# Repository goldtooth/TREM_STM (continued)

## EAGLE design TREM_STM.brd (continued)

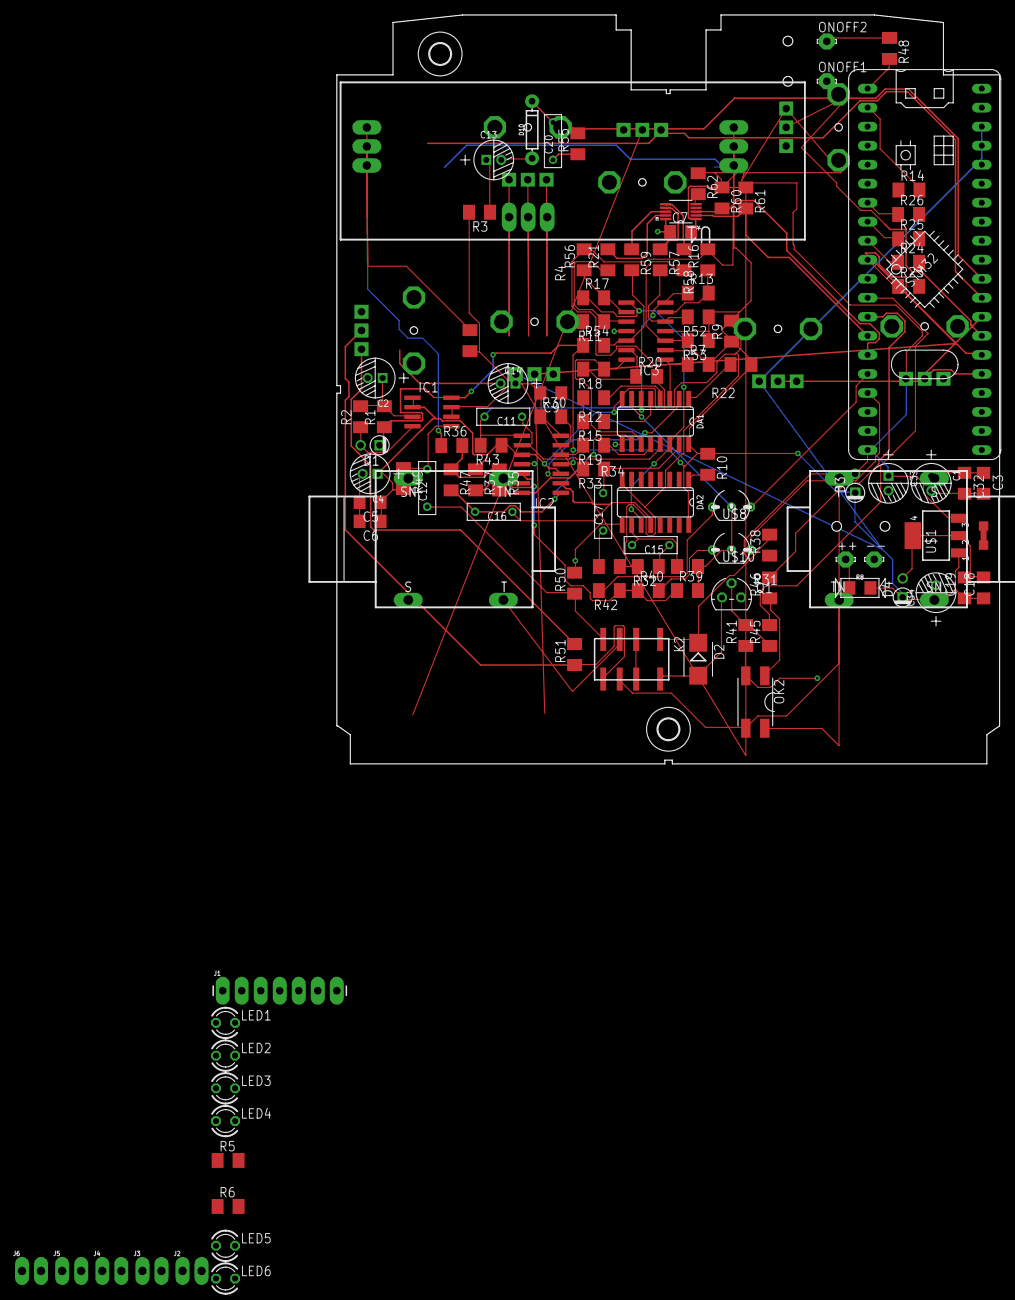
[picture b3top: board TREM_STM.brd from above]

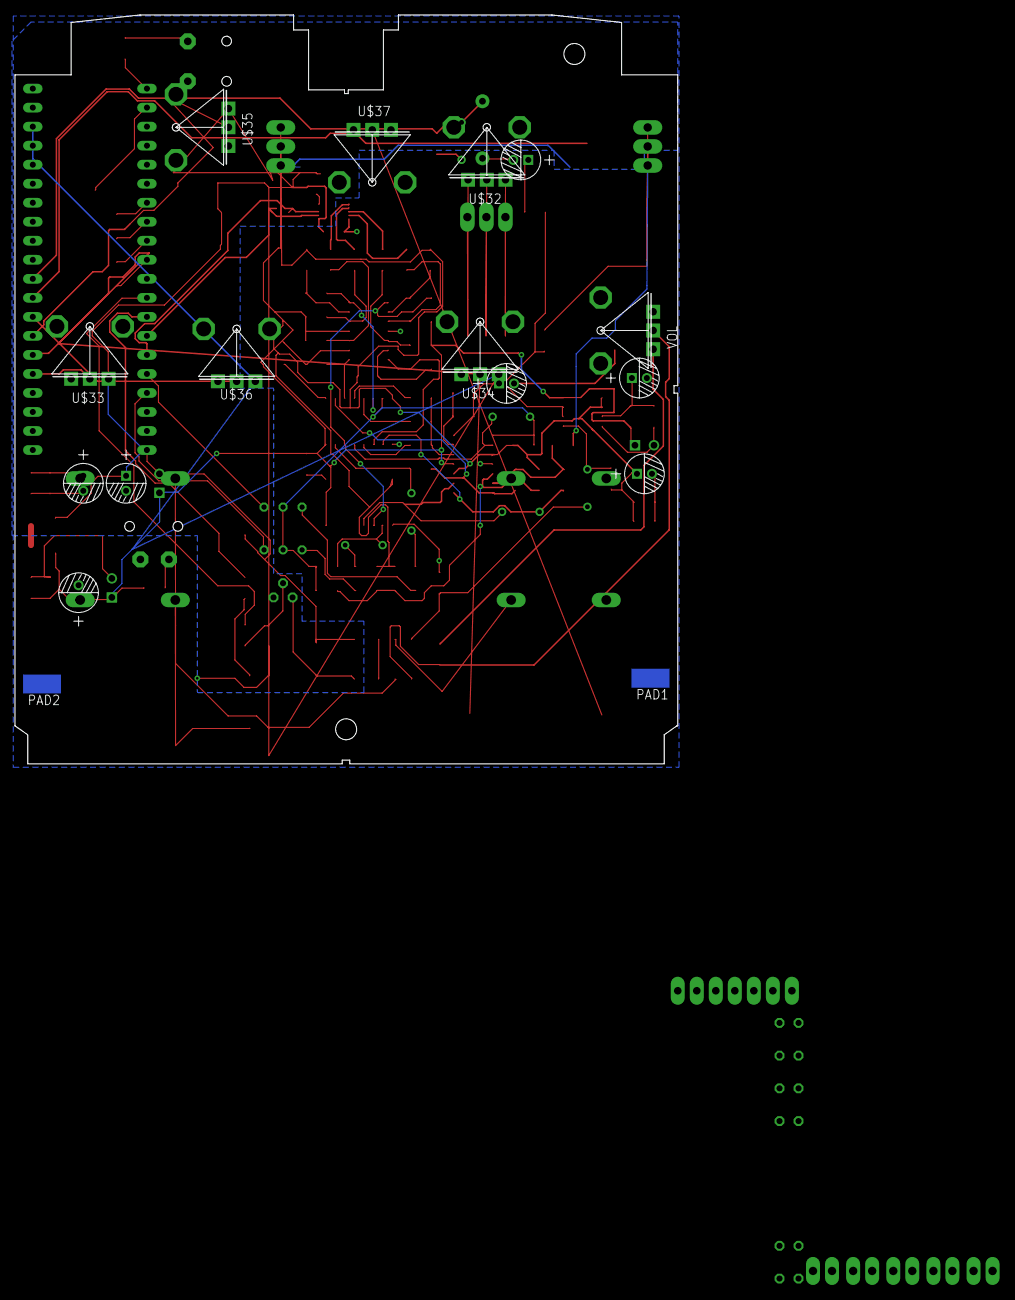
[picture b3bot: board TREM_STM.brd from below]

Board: 2 copper layers, 88.5 x 100.0 mm, 131 parts (2 on the bottom side), 93 nets.

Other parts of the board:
U$2, U$3, U$5, U$9: HOLD

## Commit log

2019-03-16 ORDERED 160319
2019-04-11 various
2019-06-23 Silent switch plus emv follower
2019-06-23 Backlink to CADLAB.io has been added.
